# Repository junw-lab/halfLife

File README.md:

Starbie

My starbie project is a tiny motion controlled pet. The parts involved include:
- Two push bottoms for interactivity
- A DHT11 environmental sensor to monitor temperature and humidity
- An OLED display module to show the sprite and let the user visually see its interaction
- An MPU6050 to give motion sensing capabilities to the starbie, allowing it to detect being moved around
- A AT42QT1010 to give the starbie a more discrete and calmer way of interaction compared to the switch

Schematic:

PCB:

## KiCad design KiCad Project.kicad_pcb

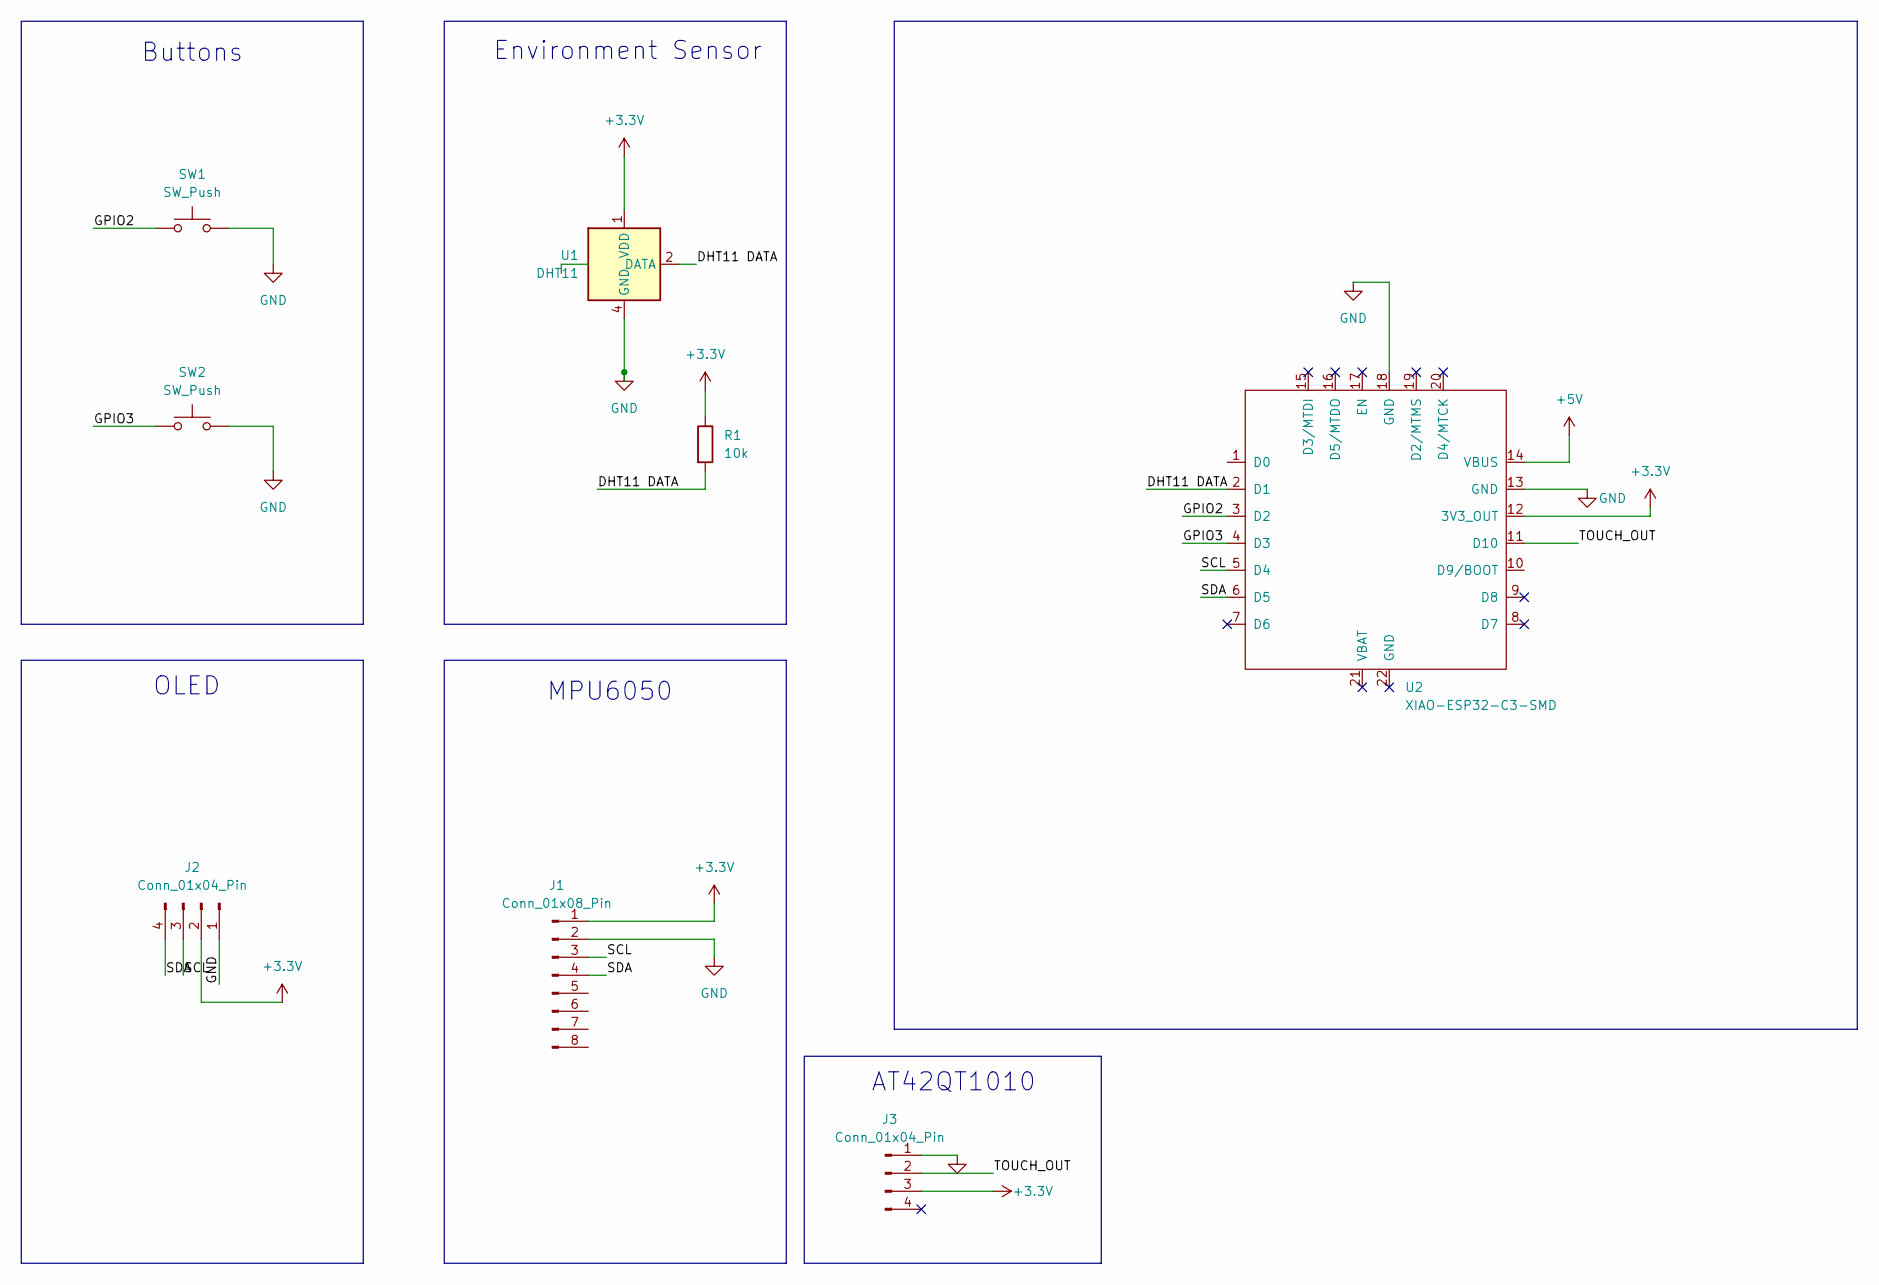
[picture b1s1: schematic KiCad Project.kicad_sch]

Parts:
J1: Conn_01x08_Pin; PinHeader_1x08_P2.54mm_Vertical
J2: Conn_01x04_Pin; Display_128x64_096_I2C
J3: Conn_01x04_Pin; PinHeader_1x04_P2.54mm_Vertical
R1: 10k; R_Axial_DIN0204_L3.6mm_D1.6mm_P7.62mm_Horizontal
SW1, SW2: SW_Push; SW_Cherry_MX_1.00u_PCB
U1: DHT11; Aosong_DHT11_5.5x12.0_P2.54mm
U2: XIAO-ESP32-C3-SMD; XIAO-ESP32-C3-DIP-SMD

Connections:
+3.3V: J1.1, J2.2, J3.3, R1.1, U1.1 (VDD), U2.12 (3V3_OUT)
+5V: U2.14 (VBUS)
/DHT11 DATA: R1.2, U1.2 (DATA), U2.2 (D1)
/GPIO2: SW1.1, U2.3 (D2)
/GPIO3: SW2.1, U2.4 (D3)
/SCL: J1.3, J2.3, U2.5 (D4)
/SDA: J1.4, J2.4, U2.6 (D5)
/TOUCH_OUT: J3.2, U2.11 (D10)
GND: J1.2, J2.1, J3.1, SW1.2, SW2.2, U1.4 (GND), U2.13 (GND), U2.18 (GND)

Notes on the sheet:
AT42QT1010
OLED
Buttons
Environment Sensor
MPU6050

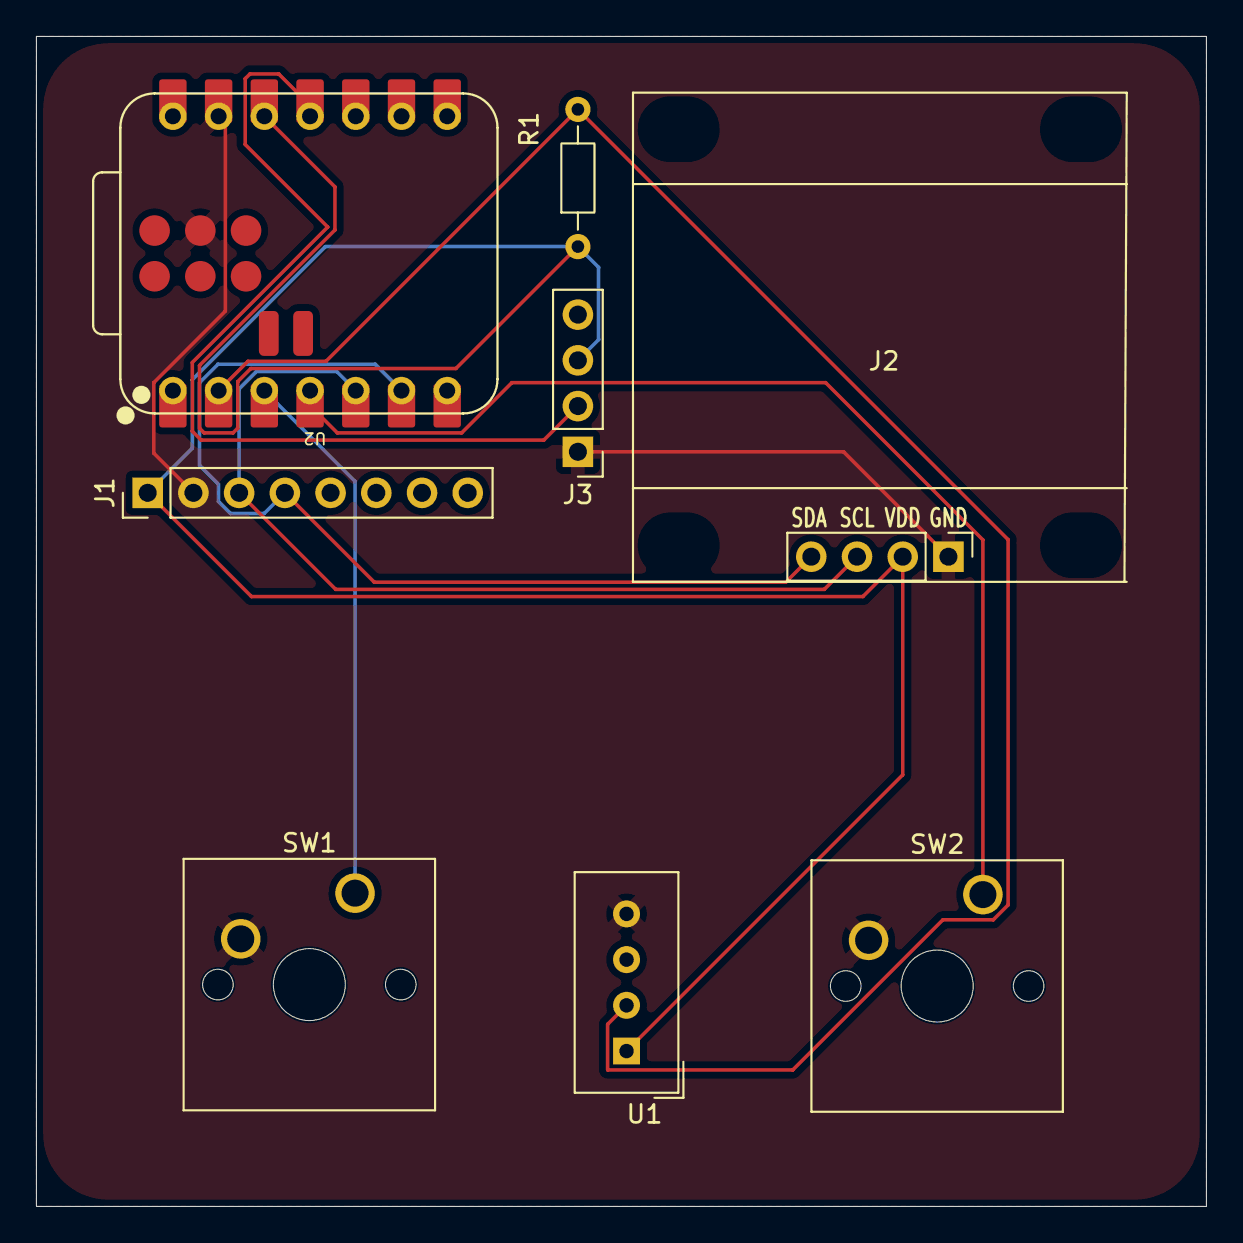
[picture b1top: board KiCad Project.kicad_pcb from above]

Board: 2 copper layers, 65.0 x 65.0 mm, 8 parts (0 on the bottom side), 8 nets.
